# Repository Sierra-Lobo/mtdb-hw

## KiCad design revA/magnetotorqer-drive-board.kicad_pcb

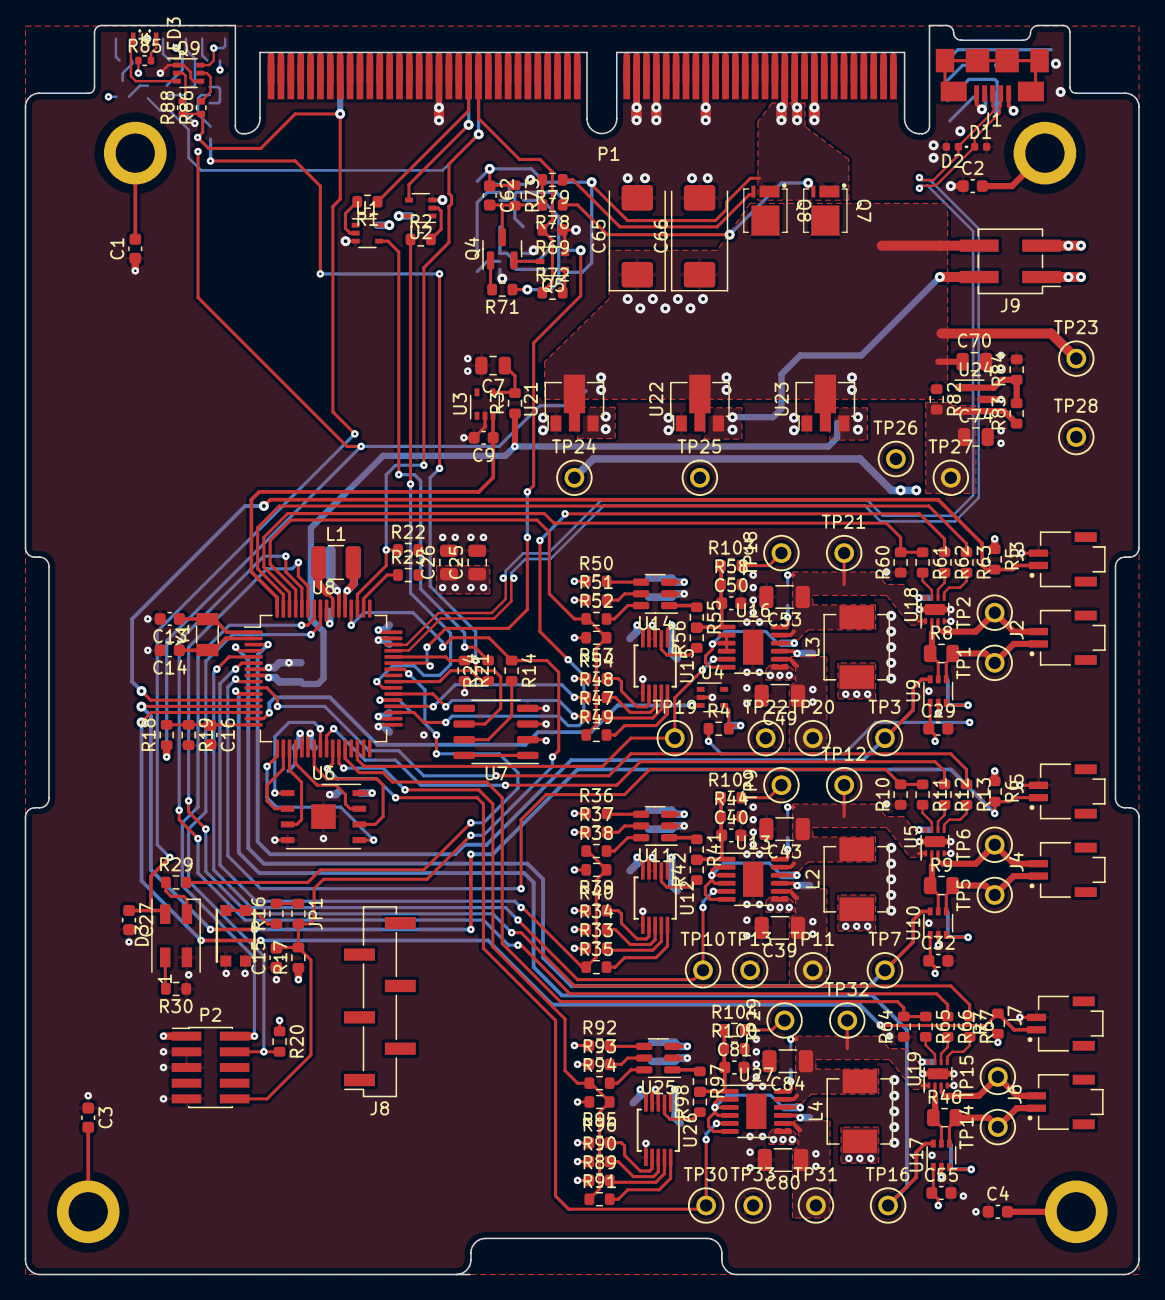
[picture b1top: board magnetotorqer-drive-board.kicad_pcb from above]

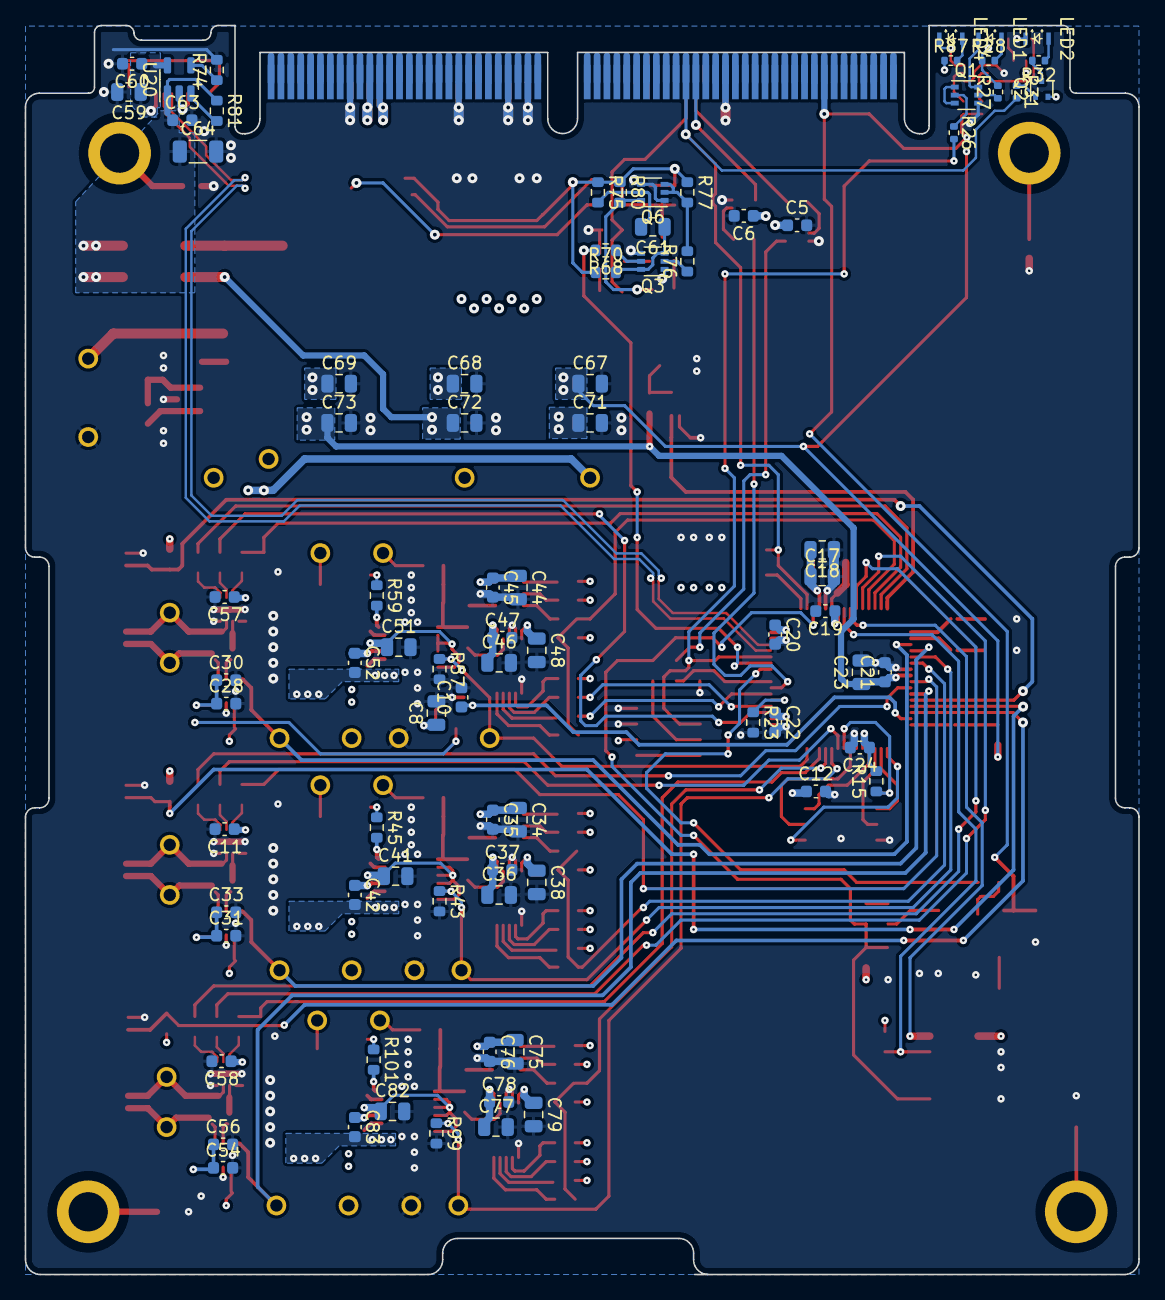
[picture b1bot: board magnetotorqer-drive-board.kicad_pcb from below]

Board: 4 copper layers, 90.2 x 101.1 mm, 283 parts (84 on the bottom side), 175 nets.

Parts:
C1, C2, C3, C4, C5, C6, C9, C10, C11, C12, C15, C16, C19, C20, C21, C22, C24, C27, C29, C30, C32, C33, C35, C37, C42, C45, C47, C52, C55, C56, C57, C58, C60, C62, C63, C76, C78, C83: 0.1uF; C_0603_1608Metric
C7, C8, C18, C38, C41, C48, C51, C67, C68, C69, C70, C71, C72, C73, C79, C82: 1uF; C_0805_2012Metric
C13, C14: 8pF; C_0603_1608Metric
C17, C23, C25, C26, C34, C36, C44, C46, C59, C61, C74, C75, C77: 10uF; C_0805_2012Metric
C28, C31, C54: 0.01uF; C_0603_1608Metric
C39, C43, C49, C53, C80, C84: 22uF; C_1206_3216Metric
C40, C50, C81: 100pF; C_0603_1608Metric
C64: 47uF; C_1206_3216Metric
C65, C66: 47uF; CP_EIA-7343-43_Kemet-X
D1, D2: ESD321DPYR; D_0402_1005Metric
D3: SK6812MINI; LED_SK6812MINI_PLCC4_3.5x3.5mm_P1.75mm
H1, H2, H3, H4: SLI-Backplane-Blank-Card-KiCad:125mil_hole; 125mil_hole
J1: ZX62-AB-5PA(31)
J2, J3, J4, J5, J6, J7: T1M-02-F-SH-L; SAMTEC_T1M-02-F-SH-L-K
J8: Conn_01x06; PinHeader_1x06_P2.54mm_Vertical_SMD_Pin1Right
J9: Conn_02x02_Top_Bottom; PinHeader_2x02_P2.54mm_Vertical_SMD
JP1: Wire Cut Jumper; R_0603_1608Metric
L1: 10uH; L_1210_3225Metric
L2, L3, L4: 2.2uH; L_Vishay_IHLP-2020
LED1: YELLOW; APA2107x
LED2: RED; APA2107x
LED3: GREEN; APA2107x
LED4: ORANGE; APA2107x
P1: Card Edge for HSEC8-160-01-S-DV-A-K-TR; HSEC8-160-CARD-EDGE
P2: FTSH-105-01-F-DV-K-TR; PinHeader_2x05_P1.27mm_Vertical_SMD
Q1, Q3, Q6, Q9: MMDT2222A; SOT-363_SC-70-6
Q2: MMBT3906T; SOT-523
Q4: IRLML2803; SOT-23
Q5: MMBT4401WT1G; SOT-323_SC-70
Q7, Q8: BSZ180; PG-TSDSON-8_3.3x3.3mm
R1, R2, R11, R12, R13, R24, R25, R33, R34, R35, R36, R37, R38, R47, R48, R49, R50, R51, R52, R61, R62, R63, R65, R66, R67, R71, R78, R79, R89, R90, R91, R92, R93, R94: 1k; R_0603_1608Metric
R3, R4: 220; R_0603_1608Metric
R5, R6, R7, R14, R15, R17, R20, R21, R22, R30, R39, R40, R53, R54, R68, R74, R81, R82, R95, R96: 10k; R_0603_1608Metric
R8, R9, R46: ${R_sense}; R_0805_2012Metric
R10, R23, R43, R44, R45, R57, R58, R59, R60, R64, R69, R70, R72, R73, R77, R99, R100, R101: 100k; R_0603_1608Metric
R16: 330; R_0603_1608Metric
R18: 330k; R_0603_1608Metric
R19: 110k; R_0603_1608Metric
R26, R27, R31, R86, R88: 10k; R_0402_1005Metric
R28, R32, R85, R87: 1.5k; R_0402_1005Metric
R29: 499; R_0603_1608Metric
R41, R42, R55, R56, R97, R98, R102, R103, R104: 0; R_0603_1608Metric
R75: 200k; R_0603_1608Metric
R76: 20k; R_0603_1608Metric
R80: 73.2k; R_0603_1608Metric
R83: 12.4k; R_0603_1608Metric
R84: 4.1k; R_0603_1608Metric
SW1: KMR231NG LFS; KMR2_4.6X2.8
TP1, TP2, TP3, TP5, TP6, TP7, TP9, TP10, TP11, TP12, TP13, TP14, TP15, TP16, TP18, TP19, TP20, TP21, TP22, TP23, TP24, TP25, TP26, TP27, TP28, TP29, TP30, TP31, TP32, TP33: ${NET_NAME(1)}; TestPoint_Keystone_5000-5004_Miniature
U1, U2: 74LVC1G17; SOT-353_SC-70-5
U3, U4: MCP9700AT-E/LT; SOT-353_SC-70-5
U5, U18, U19: DRV8838DSGT; WSON-8-1EP_2x2mm_P0.5mm_EP0.9x1.6mm
U6: MR25H10MDF; DFN-8-1EP_6x5mm_P1.27mm_EP2x2mm
U7: MAX708RESA-T; SO-8_3.9x4.9mm_P1.27mm
U8: ATSAMD51J20A-A; TQFP-64_10x10mm_P0.5mm
U9, U10, U17: INA199A2xDCK; SOT-363_SC-70-6
U11, U14, U25: DAC121S101Q; TSOT-23-6
U12, U15, U26: AD5270BRM; MSOP-10_3x3mm_P0.5mm
U13, U16, U27: LTC3600; MSOP-12-1EP_3x4mm_P0.65mm_EP1.65x2.85mm
U20: AP2161W; SOT-23-5
U21, U23: MCP1700T-33; SOT-89-3
U22: MCP1700T-50; SOT-89-3
U24: ATL431BQ; SOT-23
Y1: 32.768kHz; Crystal_SMD_3215-2Pin_3.2x1.5mm

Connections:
+1V65A: C29.1, C32.1, C55.1, C74.1, R82.2, R83.1, TP27.1, U9.1 (REF), U10.1 (REF), U17.1 (REF), U24.2 (K)
+3V3A: C21.1, C23.1, C28.1, C30.1, C31.1, C33.1, C54.1, C56.1, C73.1, R3.1, R4.1, R5.1, R6.1, R7.1, TP26.1, U8.8 (VDDANA), U9.3 (V+), U10.3 (V+), U17.3 (V+), U23.3 (VO)
+3V3D: C5.1, C6.1, C11.1, C12.1, C19.1, C20.1, C22.1, C24.1, C25.1, C26.1, C57.1, C58.1, C71.1, P2.1, R15.2, R17.1, R20.1, R39.2, R40.1, R53.2, R54.1, R87.1, R95.2, R96.1, TP24.1, U1.5 (VCC), U2.5 (VCC), U5.8 (VCC), U6.8 (VDD), U7.2 (VCC), U8.21 (VDDIOB), U8.34 (VDDIO), U8.48 (VDDIO), U8.56 (VDDIO), U18.8 (VCC), U19.8 (VCC), U21.3 (VO)
+5VA: C34.1, C35.1, C36.1, C37.1, C44.1, C45.1, C46.1, C47.1, C72.1, C75.1, C76.1, C77.1, C78.1, J9.2, TP25.1, U11.3 (VA), U12.1 (VDD), U14.3 (VA), U15.1 (VDD), U22.3 (VO), U25.3 (VA), U26.1 (VDD)
/5V_USB: C59.1, C60.1, J1.1 (VBUS), U20.5 (IN)
/Control/MISO: R23.1, U8.37 (PA18)
/Control/NEOPIXEL_DIN: R29.2, U8.42 (PA21)
/Control/QSPI/CS: R15.1, U6.1 (~CS), U8.24 (PB11)
/Control/QSPI/DATA0: U6.5 (SI), U8.17 (PA08)
/Control/QSPI/DATA1: U6.2 (SO), U8.18 (PA09)
/Control/QSPI/DATA2: U6.3 (~WP), U8.19 (PA10)
/Control/QSPI/DATA3: U6.7 (~HOLD), U8.20 (PA11)
/Control/QSPI/SCK: U6.6 (SCK), U8.23 (PB10)
/Control/SWCLK: P2.4, R20.2, U8.57 (PA30)
/Control/SWDIO: P2.2, U8.58 (PA31)
/Control/VAA_ADC: C16.1, R18.2, R19.1, U8.16 (PA07)
/Control/VDDCORE: C17.1, C18.2, L1.2, U8.53 (VDDCORE)
/Control/VSW: L1.1, U8.55 (VSW)
/Control/WDT_WDI: R21.1, R26.2, U7.6 (~WDI), U8.44 (PA23)
/Control/XTAL1: C13.1, U8.1 (PA00), Y1.1
/Control/XTAL2: C14.1, U8.2 (PA01), Y1.2
/D+: D2.1 (K), J1.3 (D+), U8.45 (PA24)
/D-: D1.1 (K), J1.2 (D-), U8.46 (PA25)
/HARD_RESET: R68.2, U8.43 (PA22)
/MOSI: R33.1, R36.1, R47.1, R50.1, R89.1, R92.1, U8.38 (PA19)
/PWR_EN: P1.44, R69.2, R72.1
/Power/~HRST: Q6.6 (C2), R71.1, R80.2
/RX: R24.2, U1.4
/RX_4: P1.41, U2.4
/SCK: R34.1, R37.1, R48.1, R51.1, R90.1, R93.1, U8.36 (PA17)
/TEMP_A: C9.1, U3.3 (V_{OUT}), U8.64 (PB03)
/TEMP_B: C10.1, U4.3 (V_{OUT}), U8.15 (PA06)
/TX: R2.1, U8.39 (PB16)
/TX_4: P1.42, R1.1
/VBATT: C62.1, P1.97, P1.98, P1.99, P1.100, Q7.1 (S), Q8.1 (S), R70.1, R73.1, R75.1, R77.1, R80.1
/X Driver/Adjustable Buck Regulator 1/BST: C52.1, U16.9 (BOOST)
/X Driver/Adjustable Buck Regulator 1/DAC_VOUT: R55.1, U14.1 (VOUT)
/X Driver/Adjustable Buck Regulator 1/DPOT_IN: R56.1, U15.2 (A)
/X Driver/Adjustable Buck Regulator 1/INTVCC: C51.1, U16.2 (ITH), U16.3 (RT), U16.4 (PGFB), U16.6 (MODE/SYNC), U16.10 (INTVCC)
/X Driver/Adjustable Buck Regulator 1/SW: C52.2, L3.1, U16.7 (SW)
/X Driver/Adjustable Buck Regulator 1/VSET: C50.1, R55.2, R56.2, R58.1, R103.1, U16.1 (ISET)
/X Driver/OUT1_SEN: R8.1, U9.5 (-), U18.2 (OUT1)
/X Driver/VDRV: C53.1, L3.2, R59.1, TP21.1, U16.11 (VOUT), U18.1 (VM)
/X+: J2.1, R8.2, TP1.1, U9.4 (+)
/X-: J2.2, TP2.1, U18.3 (OUT2)
/X_HB_PH: R63.1, U8.63 (PB02)
/X_PH_EN: R62.1, U8.35 (PA16)
/X_REG_EN: R57.1, TP19.1, U8.30 (PA13), U16.5 (RUN)
/X_TEMP: J3.1, R5.2, U8.12 (PB09)
/X_VRSEN: TP3.1, U8.3 (PA02), U9.6
/Y Driver/Adjustable Buck Regulator 1/BST: C42.1, U13.9 (BOOST)
/Y Driver/Adjustable Buck Regulator 1/DAC_VOUT: R41.1, U11.1 (VOUT)
/Y Driver/Adjustable Buck Regulator 1/DPOT_IN: R42.1, U12.2 (A)
/Y Driver/Adjustable Buck Regulator 1/INTVCC: C41.1, U13.2 (ITH), U13.3 (RT), U13.4 (PGFB), U13.6 (MODE/SYNC), U13.10 (INTVCC)
/Y Driver/Adjustable Buck Regulator 1/SW: C42.2, L2.1, U13.7 (SW)
/Y Driver/Adjustable Buck Regulator 1/VSET: C40.1, R41.2, R42.2, R44.1, R102.1, U13.1 (ISET)
/Y Driver/OUT1_SEN: R9.1, U5.2 (OUT1), U10.5 (-)
/Y Driver/VDRV: C43.1, L2.2, R45.1, TP12.1, U5.1 (VM), U13.11 (VOUT)
/Y+: J4.1, R9.2, TP5.1, U10.4 (+)
/Y-: J4.2, TP6.1, U5.3 (OUT2)
/Y_HB_PH: R13.1, U8.10 (PB07)
/Y_PH_EN: R12.1, U8.25 (PB12)
/Y_REG_EN: R43.1, TP10.1, U8.5 (PB04), U13.5 (RUN)
/Y_TEMP: J5.1, R6.2, U8.13 (PA04)
/Y_VRSEN: TP7.1, U8.4 (PA03), U10.6
/Z Driver/Adjustable Buck Regulator 1/BST: C83.1, U27.9 (BOOST)
/Z Driver/Adjustable Buck Regulator 1/DAC_VOUT: R97.1, U25.1 (VOUT)
/Z Driver/Adjustable Buck Regulator 1/DPOT_IN: R98.1, U26.2 (A)
/Z Driver/Adjustable Buck Regulator 1/INTVCC: C82.1, U27.2 (ITH), U27.3 (RT), U27.4 (PGFB), U27.6 (MODE/SYNC), U27.10 (INTVCC)
/Z Driver/Adjustable Buck Regulator 1/SW: C83.2, L4.1, U27.7 (SW)
/Z Driver/Adjustable Buck Regulator 1/VSET: C81.1, R97.2, R98.2, R100.1, R104.1, U27.1 (ISET)
/Z Driver/OUT1_SEN: R46.1, U17.5 (-), U19.2 (OUT1)
/Z Driver/VDRV: C84.1, L4.2, R101.1, TP32.1, U19.1 (VM), U27.11 (VOUT)
/Z+: J6.1, R46.2, TP14.1, U17.4 (+)
/Z-: J6.2, TP15.1, U19.3 (OUT2)
/Z_HB_PH: R67.1, U8.59 (PB30)
/Z_PH_EN: R66.1, U8.60 (PB31)
/Z_REG_EN: R99.1, TP30.1, U8.26 (PB13), U27.5 (RUN)
/Z_TEMP: J7.1, R7.2, U8.14 (PA05)
/Z_VRSEN: TP16.1, U8.11 (PB08), U17.6
/~FAULT: P1.43, R22.1, R31.2, U8.51 (PA27)
/~RST: C15.2, JP1.2 (B), P2.10, R14.1, R17.2, U8.52 (~RESET)
/~X_HB_SLEEP: R60.2, R61.1, U8.62 (PB01)
/~X_SYNC: R49.1, R52.1, R53.1, U8.61 (PB00)
/~Y_HB_SLEEP: R10.2, R11.1, U8.9 (PB06)
/~Y_SYNC: R35.1, R38.1, R39.1, U8.6 (PB05)
/~Z_HB_SLEEP: R64.2, R65.1, U8.28 (PB15)
/~Z_SYNC: R91.1, R94.1, R95.1, U8.27 (PB14)
GND: C1.1, C2.1, C3.1, C4.1, C5.2, C6.2, C7.2, C8.2, C9.2, C10.2, C11.2, C12.2, C13.2, C14.2, C15.1, C16.2, C17.2, C18.1, C19.2, C20.2, C21.2, C22.2, C23.2, C24.2, C25.2, C26.2, C27.2, C28.2, C29.2, C30.2, C31.2, C32.2, C33.2, C34.2, C35.2, C36.2, C37.2, C38.2, C39.2, C40.2, C41.2, C43.2, C44.2, C45.2, C46.2, C47.2, C48.2, C49.2, C50.2, C51.2, C53.2, C54.2, C55.2, C56.2, C57.2, C58.2, C59.2, C60.2, C63.2, C64.2, C65.2, C66.2, C67.2, C68.2, C69.2, C70.2, C71.2, C72.2, C73.2, C74.2, C75.2, C76.2, C77.2, C78.2, C79.2, C80.2, C81.2, C82.2, C84.2, D1.2 (A), D2.2 (A), D3.2 (VSS), J1.5 (GND), J3.2, J5.2, J7.2, LED2.1 (K), P1.35, P1.36, P1.67, P1.68, P1.71, P1.72, P1.81, P1.82, P1.103, P1.104, P2.3, P2.5, P2.9, Q1.4 (E1), Q3.1 (E2), Q3.4 (E1), Q5.2 (E), Q6.1 (E2), Q6.4 (E1), Q9.1 (E2), Q9.4 (E1), R10.1, R19.2, R21.2, R22.2, R23.2, R30.1, R43.2, R44.2, R57.2, R58.2, R60.1, R64.1, R69.1, R74.2, R84.2, R99.2, R100.2, SW1.2 (B), TP13.1, TP22.1, TP28.1, TP33.1, U1.3 (GND), U2.3 (GND), U3.2 (GND), U4.2 (GND), U5.4 (GND), U5.9 (GND), U6.4 (VSS), U6.9 (EP), U7.3 (GND), U7.4 (PFI), U8.7 (GNDANA), U8.22 (GND), U8.33 (GND), U8.47 (GND), U8.54 (GND), U9.2 (GND), U10.2 (GND), U11.2 (GND), U12.3 (W), U12.4 (VSS), U12.6 (GND), U13.13 (GND), U14.2 (GND), U15.3 (W), U15.4 (VSS), U15.6 (GND), U16.13 (GND), U17.2 (GND), U18.4 (GND), U18.9 (GND), U19.4 (GND), U19.9 (GND), U20.2 (GND), U21.1 (GND), U22.1 (GND), U23.1 (GND), U24.3 (A), U25.2 (GND), U26.3 (W), U26.4 (VSS), U26.6 (GND), U27.13 (GND)
LED_VCC: C27.1, D3.4 (VDD), P1.15, Q2.2 (E), R27.2, R28.1, R86.1, R88.1
unnamed: C1.2, H1.1
unnamed: C2.2, H2.1
unnamed: C3.2, H3.1
unnamed: C4.2, H4.1
unnamed: D3.3 (DIN), R29.1
unnamed: D3.1 (DOUT), R30.2
unnamed: C63.1, C64.1, J9.1, J9.3, R81.1, U20.1 (OUT)
unnamed: JP1.1 (A), R16.2
unnamed: LED1.2 (A), R28.2
unnamed: LED1.1 (K), Q1.6 (C2)
unnamed: LED2.2 (A), R32.1
unnamed: LED3.2 (A), R85.2
unnamed: LED3.1 (K), Q9.3 (C1)
unnamed: LED4.2 (A), R87.2
unnamed: LED4.1 (K), Q9.6 (C2)
unnamed: Q1.5 (B1), R27.1
unnamed: Q1.1 (E2), Q1.3 (C1)
unnamed: Q1.2 (B2), R26.1
unnamed: Q2.1 (B), R31.1
unnamed: Q2.3 (C), R32.2
unnamed: Q3.5 (B1), R68.1
unnamed: C61.1, Q3.3 (C1), Q3.6 (C2), R70.2
unnamed: Q3.2 (B2), R76.1
unnamed: C62.2, Q4.3 (D), R73.2, R78.2, R79.2
unnamed: Q4.1 (G), R71.2
unnamed: Q4.2 (S), Q5.3 (C)
unnamed: Q5.1 (B), R72.2
unnamed: C61.2, Q6.5 (B1), R75.2
unnamed: Q6.2 (B2), Q6.3 (C1), R76.2, R77.2
unnamed: Q7.4 (G), R78.1
unnamed: Q8.4 (G), R79.1
unnamed: Q9.5 (B1), R86.2
unnamed: Q9.2 (B2), R88.2
unnamed: R1.2, U1.2
unnamed: R2.2, U2.2
unnamed: R102.2, TP9.1
unnamed: R103.2, TP18.1
unnamed: R104.2, TP29.1
unnamed: R16.1, SW1.1 (A)
unnamed: C7.1, R3.2, U3.4 (V_{DD})
unnamed: C8.1, R4.2, U4.4 (V_{DD})
unnamed: R13.2, U5.5 (EN)
unnamed: R12.2, U5.6 (PH)
unnamed: R11.2, U5.7 (~SLEEP)
unnamed: U7.1 (~MR), U7.8 (~WDO)
unnamed: R14.2, U7.7 (~RESET)
unnamed: R24.1, U8.40 (PB17)
unnamed: R25.1, U8.50 (PB23)
unnamed: R36.2, U11.4 (DIN)
unnamed: R37.2, U11.5 (SCK)
unnamed: R38.2, U11.6 (~SYNC)
unnamed: R34.2, U12.8 (DIN)
unnamed: C38.1, U12.5 (EXT_CAP)
unnamed: R33.2, U12.9 (SCK)
unnamed: R40.2, U12.7 (SDO)
unnamed: R35.2, U12.10 (~SYNC)
unnamed: R45.2, U13.12 (PGOOD)
unnamed: R50.2, U14.4 (DIN)
unnamed: R51.2, U14.5 (SCK)
unnamed: R52.2, U14.6 (~SYNC)
unnamed: R48.2, U15.8 (DIN)
unnamed: C48.1, U15.5 (EXT_CAP)
unnamed: R47.2, U15.9 (SCK)
unnamed: R54.2, U15.7 (SDO)
unnamed: R49.2, U15.10 (~SYNC)
unnamed: R59.2, U16.12 (PGOOD)
unnamed: R63.2, U18.5 (EN)
unnamed: R62.2, U18.6 (PH)
unnamed: R61.2, U18.7 (~SLEEP)
unnamed: R67.2, U19.5 (EN)
unnamed: R66.2, U19.6 (PH)
unnamed: R65.2, U19.7 (~SLEEP)
unnamed: R74.1, U20.4 (~EN)
unnamed: R81.2, U20.3 (~FLG)
unnamed: R83.2, R84.1, U24.1 (REF)
unnamed: R92.2, U25.4 (DIN)
unnamed: R93.2, U25.5 (SCK)
unnamed: R94.2, U25.6 (~SYNC)
unnamed: R90.2, U26.8 (DIN)
unnamed: C79.1, U26.5 (EXT_CAP)
unnamed: R89.2, U26.9 (SCK)
unnamed: R96.2, U26.7 (SDO)
unnamed: R91.2, U26.10 (~SYNC)
unnamed: R101.2, U27.12 (PGOOD)
VAA: C39.1, C49.1, C65.1, C66.1, C67.1, C68.1, C69.1, C70.1, C80.1, J9.4, Q7.5 (D), Q8.5 (D), R18.1, R82.1, R85.1, TP11.1, TP20.1, TP23.1, TP31.1, U13.8 (VIN), U16.8 (VIN), U21.2 (VI), U22.2 (VI), U23.2 (VI), U27.8 (VIN)

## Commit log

2023-06-22 init
2023-06-24 working
2023-06-24 exported init pdf
2023-06-27 placement
2023-06-28 routing mostly complete
2023-06-30 worked review changes
